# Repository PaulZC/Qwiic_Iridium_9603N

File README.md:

# Qwiic Iridium 9603N

### We've moved!

This repo has a new home over at [SparkFun](https://github.com/sparkfun/Qwiic_Iridium_9603N)

_"So long, and thanks for all the fish."_
_(Douglas Adams)_

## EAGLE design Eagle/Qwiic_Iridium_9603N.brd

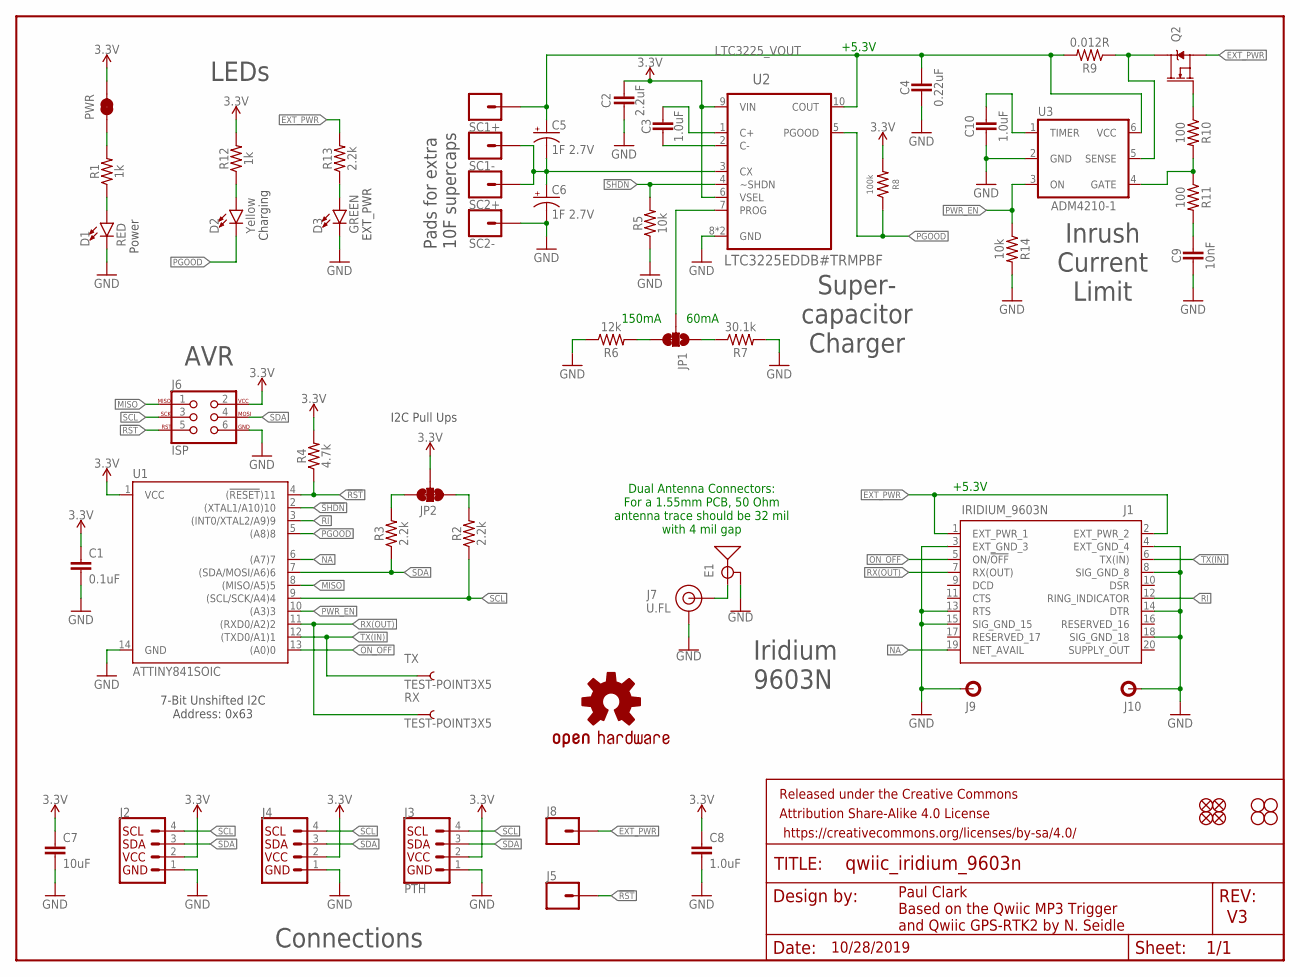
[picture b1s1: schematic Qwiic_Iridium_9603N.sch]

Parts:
C1: 0.1uF; 0603
C2: 2.2uF; 0603
C3, C8, C10: 1.0uF; 0603
C4: 0.22uF; 0603
C5, C6: 1F 2.7V; CPOL-RADIAL-1F-2.7V
C7: 10uF; 0603
C9: 10nF; 0603
D1: RED; LED-0603
D2: Yellow; LED-0603
D3: GREEN; LED-0603
E1: ANTENNA-GROUNDEDEDGE_SMA; SMA-EDGE
FRAME1: FRAME-LETTER; CREATIVE_COMMONS
J1: IRIDIUM_9603N
J2, J4: QWIIC_CONNECTORJS-1MM; JST04_1MM_RA
J3: PTH; 1X04_NO_SILK
J5, J8: CONN_01PTH_NO_SILK_YES_STOP; 1X01_NO_SILK
J6: ISP; 2X3_TEST_POINTS
J7: U.FL
J9, J10: STANDOFFS_M2X0.4_STEEL_6MM; STANDOFF_M2X0.4
JP1: JUMPER-SMT_3_1-NC_TRACE_SILK; SMT-JUMPER_3_1-NC_TRACE_SILK
JP2: JUMPER-SMT_3_2-NC_TRACE_SILK; SMT-JUMPER_3_2-NC_TRACE_SILK
JP3, JP4, JP9, JP10: STAND-OFF
JP5, JP6, JP7, JP8: FIDUCIAL1X2; FIDUCIAL-1X2
LOGO1: OSHW-LOGOMINI; OSHW-LOGO-MINI
PWR: JUMPER-SMT_2_NC_TRACE_SILK; SMT-JUMPER_2_NC_TRACE_SILK
Q2: 5.8A/30V/35mΩ; SOT23-3
R1, R12: 1k; 0603
R2, R3, R13: 2.2k; 0603
R4: 4.7k; 0603
R5, R14: 10k; 0603
R6: 12k; 0603
R7: 30.1k; 0603
R8: 100k; 0603
R9: 0.012R; 0603
R10, R11: 100; 0603
RX: TEST-POINT3X5; PAD.03X.05
SC1+, SC1-, SC2+, SC2-: CONN_01PTH_NO_SILK_YES_STOP; 1X01_NO_SILK
TX: TEST-POINT3X5; PAD.03X.05
U1: ATTINY841SOIC; ATTINY841
U2: LTC3225EDDB#TRMPBF; DFN300X200-10L
U3: ADM4210-1; TSOT6

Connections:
3.3V: C1.1, C2.1, C7.1, C8.1, J2.2, J3.2 (VCC), J4.2, J6.2, JP2.2, PWR.2, R4.2, R8.2, R12.2, U1.1 (VCC), U2.6 (VSEL), U2.9 (VIN)
!RST: J5.1, J6.5, R4.1, U1.4 ((!RESET!)11)
!SHDN: R5.2, U1.2 ((XTAL1/A10)10), U2.4 (~SHDN)
EXT_PWR: J1.1 (EXT_PWR_1), J1.2 (EXT_PWR_2), J8.1, Q2.2 (S), R13.2
GND: C1.2, C2.2, C4.2, C6.-, C7.2, C8.2, C9.2, C10.2, D1.C, D3.C, E1.GND@0 (GND), E1.GND@1 (GND), E1.GND@2 (GND), E1.GND@3 (GND), J1.3 (EXT_GND_3), J1.4 (EXT_GND_4), J1.8 (SIG_GND_8), J1.13 (RTS), J1.14 (DTR), J1.15 (SIG_GND_15), J1.18 (SIG_GND_18), J2.1, J3.1 (GND), J4.1, J6.6, J7.1 (GND), J7.2 (GND), J9.1, J10.1, R5.1, R6.1, R7.2, R14.2, SC2-.1, U1.14 (GND), U2.8 (GND), U2.11 (GND), U3.2 (GND)
LTC3225_VOUT: C4.1, C5.+, R9.2, SC1+.1, U2.10 (COUT), U3.6 (VCC)
MISO: J6.1, U1.8 ((MISO/A5)5)
unnamed: C5.-, C6.+, SC1-.1, SC2+.1, U2.3 (CX)
unnamed: JP1.3, R6.2
unnamed: D1.A, R1.1
unnamed: JP1.1, R7.1
unnamed: D2.A, R12.1
unnamed: D3.A, R13.1
unnamed: E1.SIG (SIGNAL), J7.FEED (SIGNAL)
unnamed: Q2.3 (D), R9.1, U3.5 (SENSE)
unnamed: C3.2, U2.2 (C-)
unnamed: C3.1, U2.1 (C+)
unnamed: JP1.2, U2.7 (PROG)
unnamed: Q2.1 (G), R10.1
unnamed: R10.2, R11.1, U3.4 (GATE)
unnamed: C9.1, R11.2
unnamed: C10.1, U3.1 (TIMER)
unnamed: PWR.1, R1.2
NA: J1.19 (NET_AVAIL), U1.6 ((A7)7)
ON_OFF: J1.5 (ON/!OFF!), U1.13 ((A0)0)
PGOOD: D2.C, R8.1, U1.5 ((A8)8), U2.5 (PGOOD)
PWR_EN: R14.1, U1.10 ((A3)3), U3.3 (ON)
RI: J1.12 (RING_INDICATOR), U1.3 ((INT0/XTAL2/A9)9)
RX(OUT): J1.7 (RX(OUT)), RX.P$1, U1.11 ((RXD0/A2)2)
SCL: J2.4, J3.4 (SCL), J4.4, J6.3, R2.1, U1.9 ((SCL/SCK/A4)4)
SCL_PU1: JP2.1, R2.2
SDA: J2.3, J3.3 (SDA), J4.3, J6.4, R3.1, U1.7 ((SDA/MOSI/A6)6)
SDA_PU1: JP2.3, R3.2
TX(IN): J1.6 (TX(IN)), TX.P$1, U1.12 ((TXD0/A1)1)

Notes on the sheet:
Paul Clark Based on the Qwiic MP3 Trigger and Qwiic GPS-RTK2 by N. Seidle
Power
7-Bit Unshifted I2C Address: 0x63
I2C Pull Ups
AVR
Connections
+5.3V
150mA
60mA
Pads for extra 10F supercaps
Super- capacitor Charger
Charging
EXT_PWR
Iridium 9603N
Dual Antenna Connectors: For a 1.55mm PCB, 50 Ohm antenna trace should be 32 mil with 4 mil gap
LEDs
Inrush Current Limit
10/28/2019

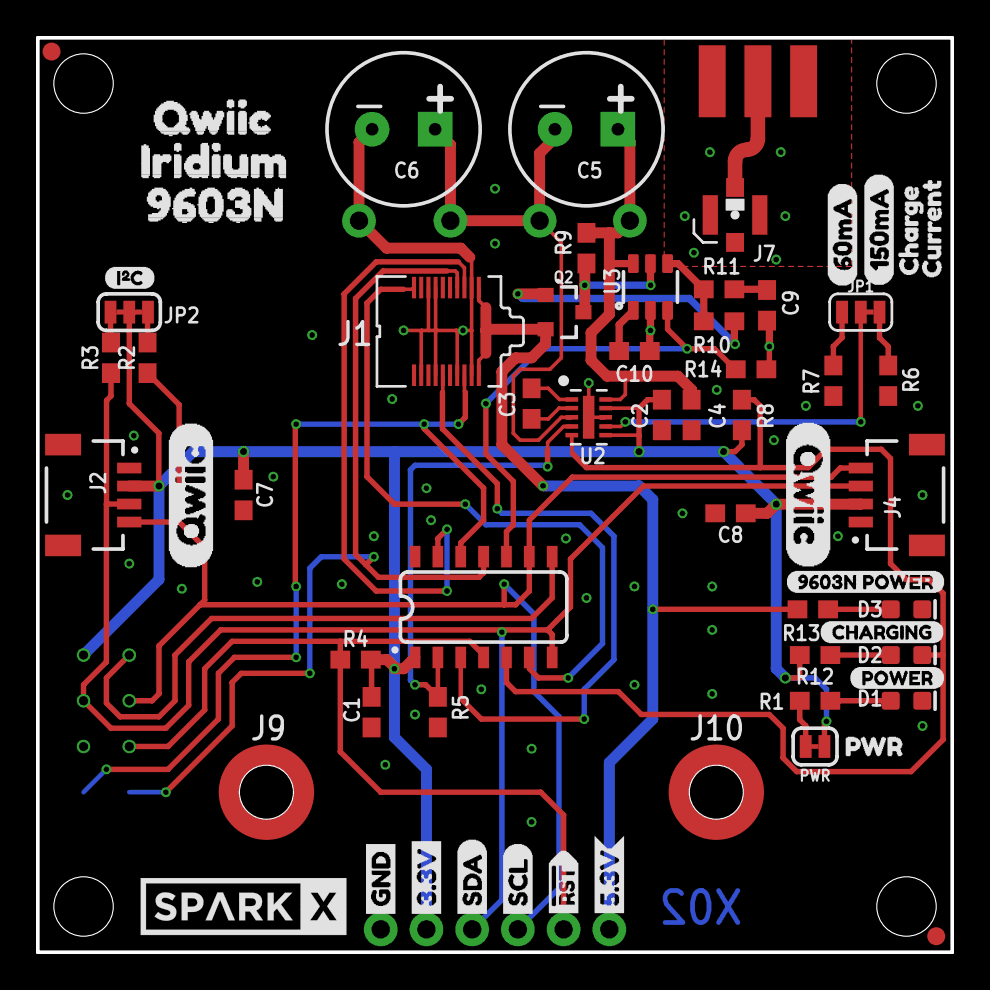
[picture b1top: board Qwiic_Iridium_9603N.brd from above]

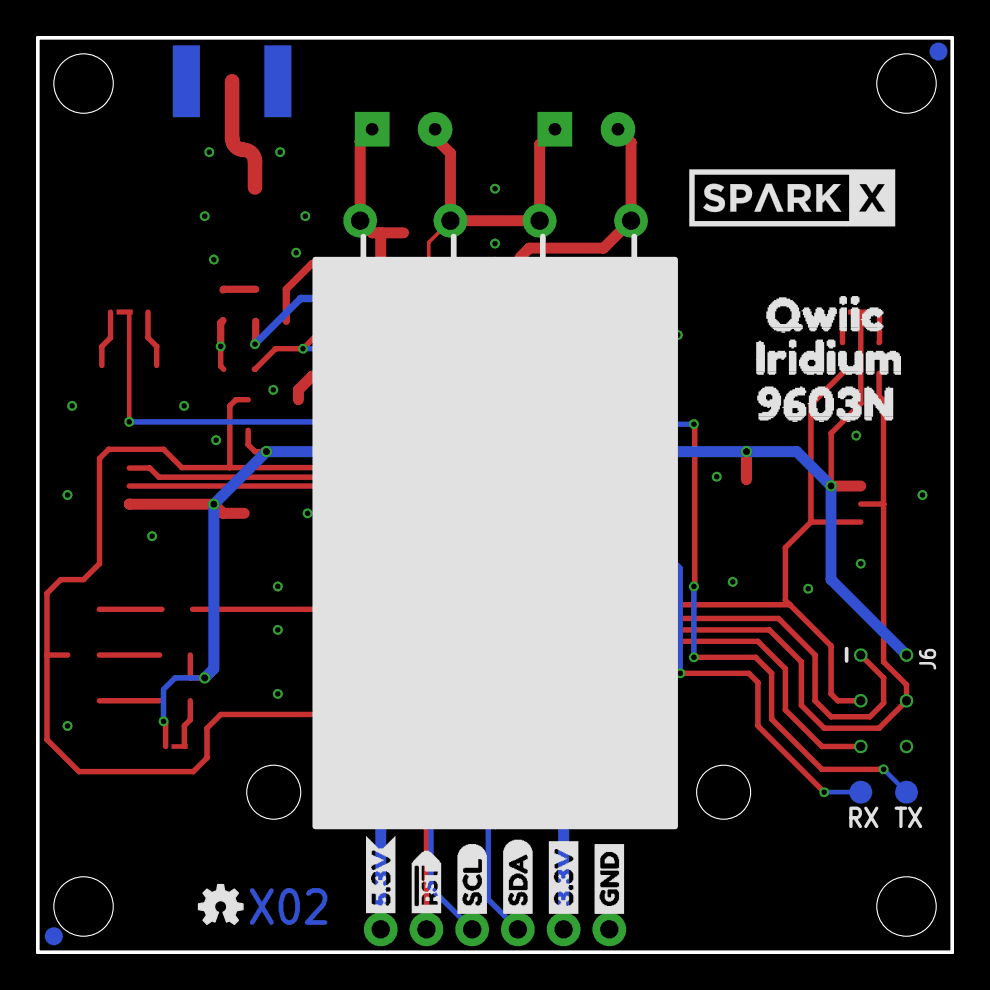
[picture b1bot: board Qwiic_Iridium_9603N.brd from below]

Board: 2 copper layers, 50.8 x 50.8 mm, 92 parts (16 on the bottom side), 34 nets.

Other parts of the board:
U$1: 60MA0
U$2: POWER0
U$3, U$22: GND1
U$4, U$21: 3#3V2
U$5, U$27: SDA8
U$6, U$26: SCL9
U$7, U$16: RST#-[>
U$8: I_SUPER2_C-()-03
U$9: CHARGING0
U$10: 9603N_POWER0
U$11, U$32: 5#3V0
U$12, U$17, U$23, U$25: QWIIC0
U$13: 150MA0
U$14: CHARGE0
U$15: CURRENT0
U$18, U$19: IRIDIUM0
U$20, U$24: 9603N0
U$29, U$30: SPARKX-LARGE
U$31: _PWR1

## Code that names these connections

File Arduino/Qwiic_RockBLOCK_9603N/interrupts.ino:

//Handle a write to the IO pins _or_ the Serial port
void receiveEvent(int numberOfBytesReceived) {
  if (Wire.available()) {
    
    byte incoming = Wire.read(); // Read the first byte

    if (incoming == SET_IO) { // Does the Master want to set the I/O pins?
      if (Wire.available()) { // Did the Master send the second byte?
        incoming = Wire.read(); // Read the second byte

        if (incoming & IO_SHDN) { // If the SHDN bit is ON
          digitalWrite(SHDN, SHDN__ON); // Turn the pin ON
        }
        else {
          digitalWrite(SHDN, SHDN__OFF); // Turn the pin OFF
        }
        
        if (incoming & IO_PWR_EN) { // If the PWR_EN bit is ON
          digitalWrite(PWR_EN, PWR_EN__ON); // Turn the pin ON
        }
        else {
          digitalWrite(PWR_EN, PWR_EN__OFF); // Turn the pin OFF
        }
        
        if (incoming & IO_ON_OFF) { // If the ON_OFF bit is ON
          digitalWrite(ON_OFF, ON_OFF__ON); // Turn the pin ON
        }
        else {
          digitalWrite(ON_OFF, ON_OFF__OFF); // Turn the pin OFF
        }
        
        if (incoming & IO_RI) { // If the RI bit is ON
          RI_FLAG = false; // Clear the RI flag
        }
      } 
    }

    else if (incoming == WR_9603) { // Does the Master want to write serial data to the 9603N?      
      while (Wire.available()) { // Read all bytes and echo them to the serial port
        byte incoming = Wire.read();
        ssIridium.write(incoming);
      }      
    }
    
    else {
      ; //Something bad happened! The first byte was not SET_IO or WR_9603...
    }
  }
}

//Handle a read of the IO 'register' and the Serial port
void requestEvent()
{
  // Read the IO pins one at a time and set or clear bits in IO_REG appropriately
  
  if (digitalRead(SHDN) == SHDN__ON) { // If the SHDN pin is in its ON state (not necessarily that it is HIGH)
    IO_REG |= IO_SHDN; // Set the SHDN bit in IO_REG
  }
  else {
    IO_REG &= ~IO_SHDN; // Clear the SHDN bit in IO_REG
  }
  
  if (digitalRead(PWR_EN) == PWR_EN__ON) { // If the PWR_EN pin is in its ON state (not necessarily that it is HIGH)
    IO_REG |= IO_PWR_EN; // Set the PWR_EN bit in IO_REG
  }
  else {
    IO_REG &= ~IO_PWR_EN; // Clear the PWR_EN bit in IO_REG
  }
  
  if (digitalRead(ON_OFF) == ON_OFF__ON) { // If the ON_OFF pin is in its ON state (not necessarily that it is HIGH)
    IO_REG |= IO_ON_OFF; // Set the ON_OFF bit in IO_REG
  }
  else {
    IO_REG &= ~IO_ON_OFF; // Clear the ON_OFF bit in IO_REG
  }
  
  if (RI_FLAG == true) { // If the RI_FLAG is true (set by the ISR)
    IO_REG |= IO_RI; // Set the RI bit in IO_REG
  }
  else {
    IO_REG &= ~IO_RI; // Clear the RI bit in IO_REG
  }
  
  if (digitalRead(NA) == NA__ON) { // If the NA pin is in its ON state (not necessarily that it is HIGH)
    IO_REG |= IO_NA; // Set the NA bit in IO_REG
  }
  else {
    IO_REG &= ~IO_NA; // Clear the NA bit in IO_REG
  }
  
  if (digitalRead(PGOOD) == PGOOD__ON) { // If the PGOOD pin is in its ON state (not necessarily that it is HIGH)
    IO_REG |= IO_PGOOD; // Set the PGOOD bit in IO_REG
  }
  else {
    IO_REG &= ~IO_PGOOD; // Clear the PGOOD bit in IO_REG
  }

  // Now write IO_REG to I2C
  Wire.write(IO_REG);

  while (ssIridium.available()) { // Now read all available serial bytes (if any) and forward them via I2C
    byte outgoing = ssIridium.read();
    Wire.write(outgoing);
  }
}

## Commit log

2019-07-07 Typo correction
2019-07-08 Updated the PCB and included the Arduino code
2019-07-08 Fixed a typo
2019-07-15 Added the BOM
2019-07-15 Corrected the BOM file type
2019-07-17 Updates for V2 of the PCB
2019-08-18 Substantial update after testing the PCB
2019-08-18 Added a read-modify-write example for IO_REG
2019-08-18 Corrected the RI polarity
2019-08-21 Added the ADM4210
2019-08-24 Added the Beacon_I2C example
2019-08-27 LTC3225 now disabled duirng setup
2019-09-03 Added assembly details for V3 of the PCB
2019-09-03 Minor corrections
2019-09-22 V1.1: Added the low power mode
2019-09-22 Added more assembly photos
2019-10-10 SparkX version of Qwiic Iridium
    Updated SKU's, silkscreens, and some superficial footprint changes.
2019-10-28 Generated PDF and cleaned up schematic
2019-10-28 Updating BOM
2020-01-15 Add ignore. Remove old backup files. Move TPs to bottom of board.
2020-01-15 Update connector footprint: reduce cream, extend copper, remove extra silk.
2020-01-15 Change connector to use SMD reflowable standoffs
2020-01-15 Reduce cream under LTC3225 IC.
2020-01-17 Reduce stopmask around connector pads. Increase standoff drill size from 3.7mm to 3.73mm.
2020-01-21 Update modem FP with Wurth part.
2020-03-22 Deleted the unwanted files
2020-03-22 Dereferenced the BOM
2020-03-22 Updated the SMD standoffs
    Updated the Iridium 9603N and the SMD standoffs. The standoffs will now appear in the BOM.
    Updated the PROD_IDs for the New_Parts.
    The component positions should all be exactly the same, so no need to update the production panel.
2020-03-25 Updated the PROD_IDs
2020-05-30 Added the link to the SparkFun repo

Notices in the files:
parts and their libraries:
SparkFun-Resistors: Licensing: Creative Commons ShareAlike 4.0 International - https://creativecommons.org/licenses/by-sa/4.0
SparkFun-Aesthetics: Released under the Creative Commons Attribution Share-Alike 4.0 License
SparkFun-Aesthetics: https://creativecommons.org/licenses/by-sa/4.0
